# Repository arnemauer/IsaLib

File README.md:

IsaLib
======

ISA Home control

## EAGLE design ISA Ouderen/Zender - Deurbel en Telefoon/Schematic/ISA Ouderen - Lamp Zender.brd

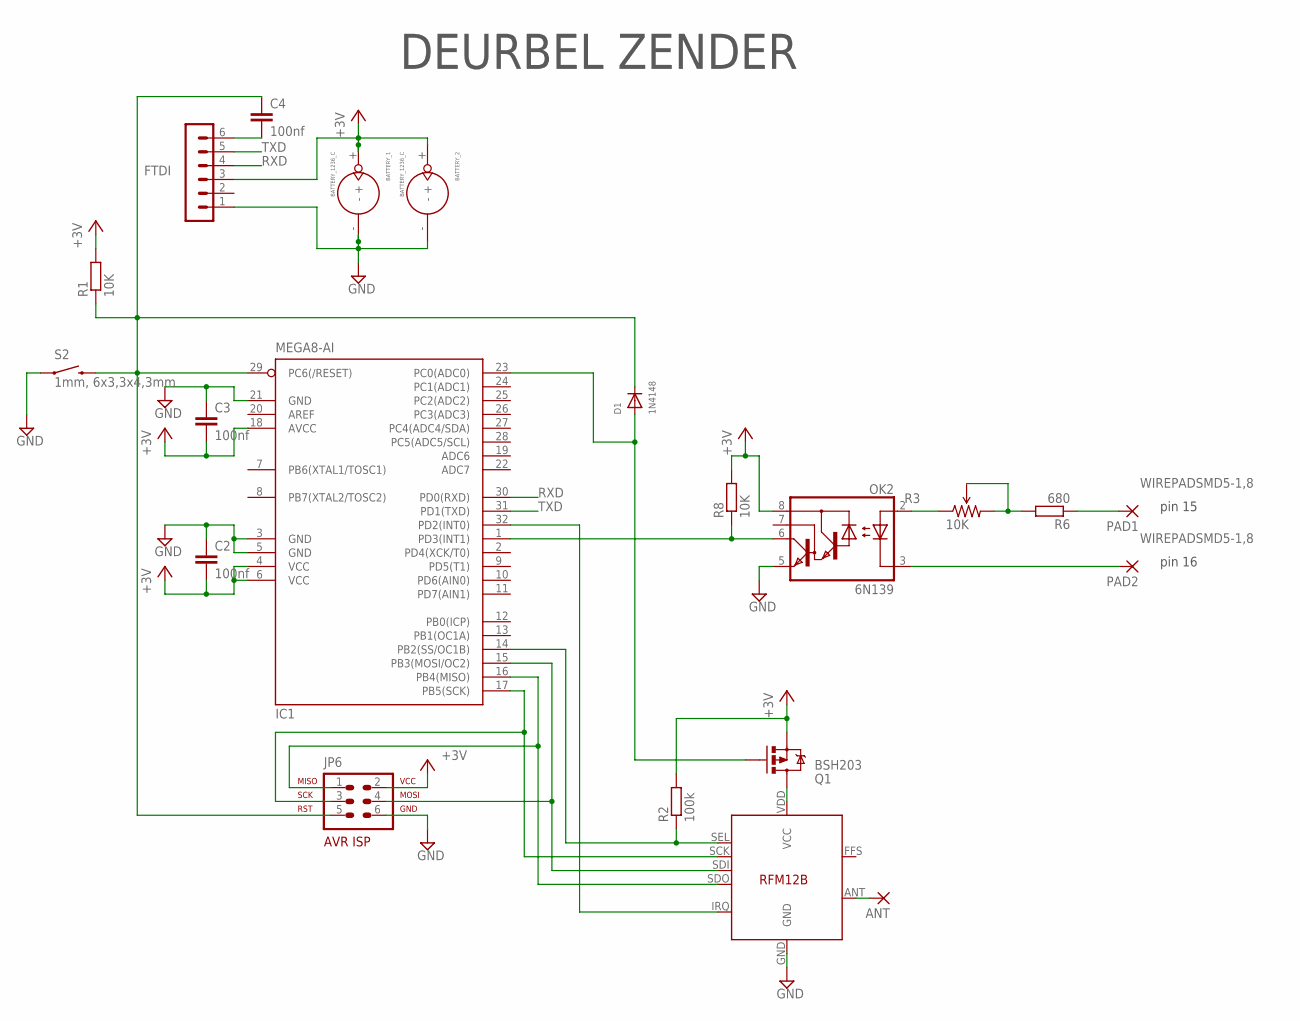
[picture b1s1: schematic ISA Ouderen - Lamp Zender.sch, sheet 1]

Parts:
ANT: 1,6/0,8
BATTERY_1, BATTERY_2: BATTERY_1236_C
C2, C3, C4: 100nf; C0805
D1: 1N4148; SOD-323F
FTDI: FTDI; MA06-1
IC1: MEGA8-AI; TQFP32-08@1
JP6: AVR-ISP-6VERT; AVR-ISP-6
OK2: 6N139; SOIC08
PAD1, PAD2: WIREPADSMD5-1,8; 5-1,8
Q1: BSH203; SOT23
R1, R8: 10K; R0805
R2: 100k; R0805
R3: 10K; TRIMPOT-5MM-V2
R6: 680; R0805
S2: 1mm, 6x3,3x4,3mm; TACTILE-SWITCH-1101NE
U$3: RFM12B

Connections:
+3V3: BATTERY_1.+, BATTERY_2.+, C2.2, C3.2, FTDI.3, IC1.4 (VCC), IC1.6 (VCC), IC1.18 (AVCC), JP6.2, OK2.8 (VCC), Q1.2 (S), R1.2, R2.2, R8.2; also elsewhere on the board
GND: BATTERY_1.-, BATTERY_2.-, C2.1, C3.1, FTDI.1, IC1.3 (GND), IC1.5 (GND), IC1.21 (GND), JP6.6, OK2.5 (GND), S2.P$1 (1), U$3.GND; also elsewhere on the board
unnamed: Q1.3 (D), U$3.VDD (VCC)
unnamed: D1.A, IC1.23 (PC0(ADC0)), Q1.1 (G)
unnamed: ANT.1, U$3.ANT
unnamed: IC1.14 (PB2(SS/OC1B)), R2.1, U$3.SEL
unnamed: IC1.32 (PD2(INT0)), U$3.IRQ
unnamed: PAD1.1, R6.1
unnamed: IC1.16 (PB4(MISO)), JP6.1, U$3.SDO
unnamed: OK2.2 (A), R3.A (CCW)
unnamed: IC1.17 (PB5(SCK)), JP6.3, U$3.SCK
unnamed: C4.2, FTDI.6
unnamed: OK2.3 (C), PAD2.1
unnamed: IC1.1 (PD3(INT1)), OK2.6 (VO), R8.1
unnamed: R3.B (WIPER), R3.C (CW), R6.2
unnamed: IC1.15 (PB3(MOSI/OC2)), JP6.4, U$3.SDI
RST: C4.1, D1.C, IC1.29 (PC6(/RESET)), JP6.5, R1.1, S2.P$2 (2)
RXD: FTDI.4, IC1.30 (PD0(RXD)); also elsewhere on the board
TXD: FTDI.5, IC1.31 (PD1(TXD)); also elsewhere on the board

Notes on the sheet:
pin 15
pin 16
DEURBEL ZENDER

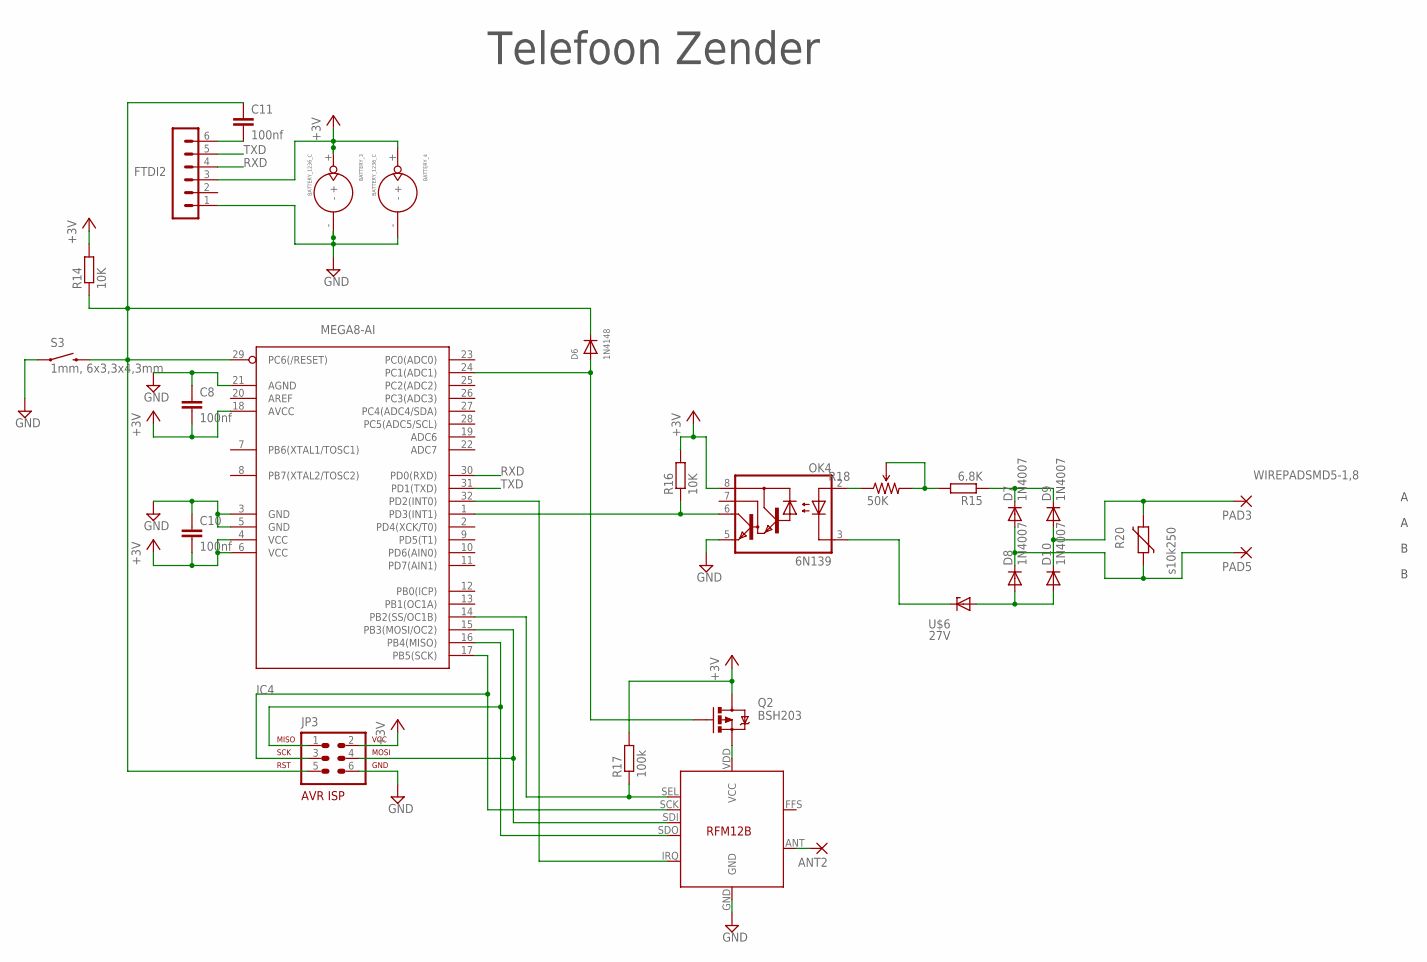
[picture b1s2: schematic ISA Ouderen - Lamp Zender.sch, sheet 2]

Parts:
ANT2: 1,6/0,8
BATTERY_3, BATTERY_4: BATTERY_1236_C
C8, C10, C11: 100nf; C0805
D6: 1N4148; SOD-323F
D7, D8, D9, D10: 1N4007; DO214BA
FTDI2: FTDI; MA06-1
IC4: MEGA8-AI; TQFP32-08
JP3: AVR-ISP-6VERT; AVR-ISP-6
OK4: 6N139; SOIC08
PAD3, PAD5: WIREPADSMD5-1,8; 5-1,8
Q2: BSH203; SOT23
R14, R16: 10K; R0805
R15: 6.8K; R0805
R17: 100k; R0805
R18: 50K; TRIMPOT-5MM-V2
R20: s10k250; R-7,5
S3: 1mm, 6x3,3x4,3mm; TACTILE-SWITCH-1101NE
U$5: RFM12B
U$6: 27V; ZDIO-2.5

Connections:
+3V3: BATTERY_3.+, BATTERY_4.+, C8.2, C10.2, FTDI2.3, IC4.4 (VCC), IC4.6 (VCC), IC4.18 (AVCC), JP3.2, OK4.8 (VCC), Q2.3 (D), R14.2, R16.2, R17.2; also elsewhere on the board
GND: BATTERY_3.-, BATTERY_4.-, C8.1, C10.1, FTDI2.1, IC4.3 (GND), IC4.5 (GND), IC4.21 (AGND), JP3.6, OK4.5 (GND), S3.P$1 (1), U$5.GND; also elsewhere on the board
unnamed: IC4.14 (PB2(SS/OC1B)), R17.1, U$5.SEL
unnamed: IC4.32 (PD2(INT0)), U$5.IRQ
unnamed: C11.2, FTDI2.6
unnamed: IC4.15 (PB3(MOSI/OC2)), JP3.4, U$5.SDI
unnamed: ANT2.1, U$5.ANT
unnamed: IC4.16 (PB4(MISO)), JP3.1, U$5.SDO
unnamed: IC4.17 (PB5(SCK)), JP3.3, U$5.SCK
unnamed: OK4.2 (A), R18.A (CCW)
unnamed: OK4.3 (C), U$6.C
unnamed: IC4.1 (PD3(INT1)), OK4.6 (VO), R16.1
unnamed: R15.2, R18.B (WIPER), R18.C (CW)
unnamed: Q2.2 (S), U$5.VDD (VCC)
unnamed: D6.A, IC4.24 (PC1(ADC1)), Q2.1 (G)
unnamed: D9.A, D10.C, PAD3.1, R20.2
unnamed: D7.A, D8.C, PAD5.1, R20.1
unnamed: D8.A, D10.A, U$6.A
unnamed: D7.C, D9.C, R15.1
RST2: C11.1, D6.C, IC4.29 (PC6(/RESET)), JP3.5, R14.1, S3.P$2 (2)
RXD: FTDI2.4, IC4.30 (PD0(RXD)); also elsewhere on the board
TXD: FTDI2.5, IC4.31 (PD1(TXD)); also elsewhere on the board

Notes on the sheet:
Telefoon Zender

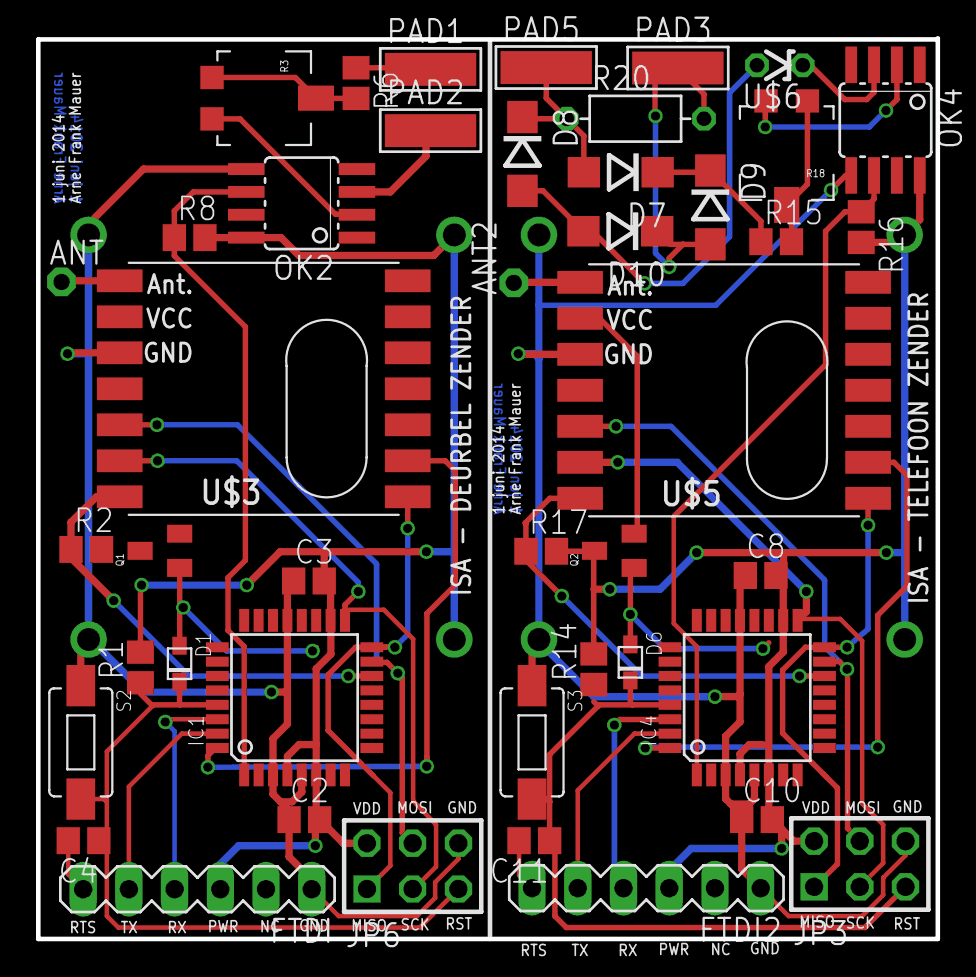
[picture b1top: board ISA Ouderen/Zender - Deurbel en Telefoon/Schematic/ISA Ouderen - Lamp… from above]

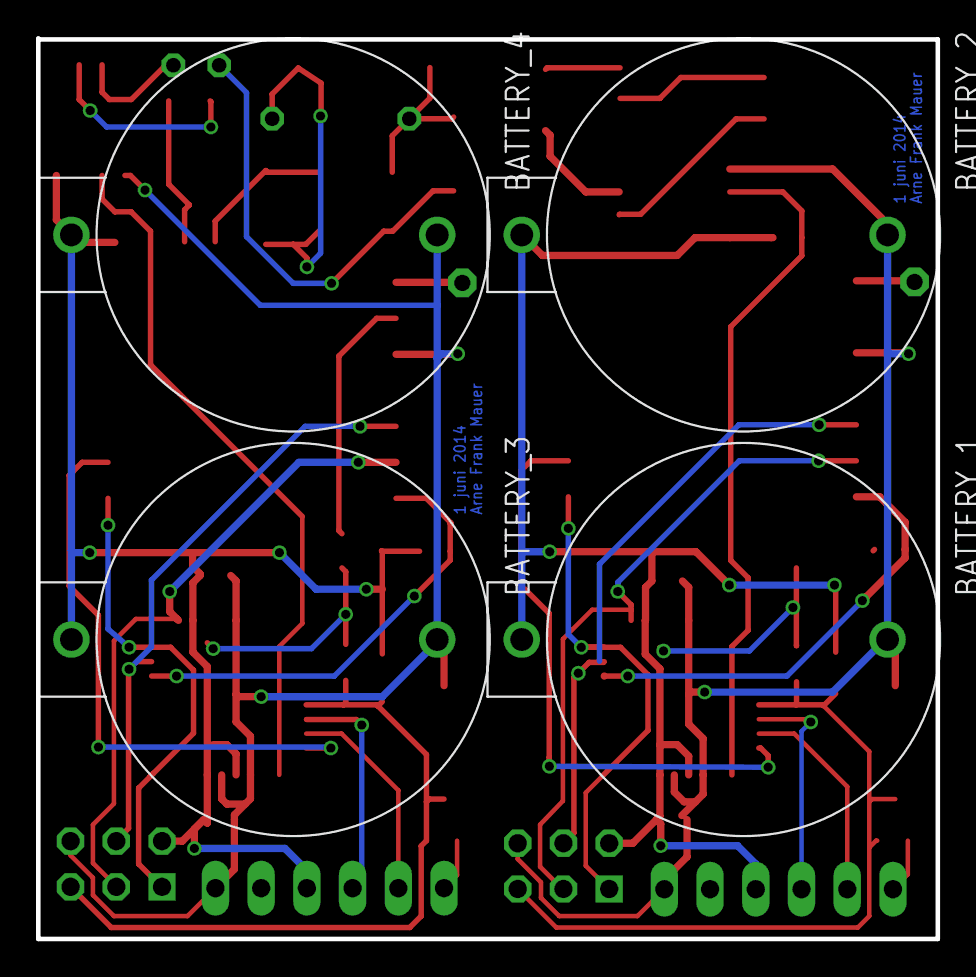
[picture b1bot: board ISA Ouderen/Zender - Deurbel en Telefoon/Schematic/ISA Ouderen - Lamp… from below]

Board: 2 copper layers, 50.0 x 50.0 mm, 48 parts (4 on the bottom side), 37 nets.

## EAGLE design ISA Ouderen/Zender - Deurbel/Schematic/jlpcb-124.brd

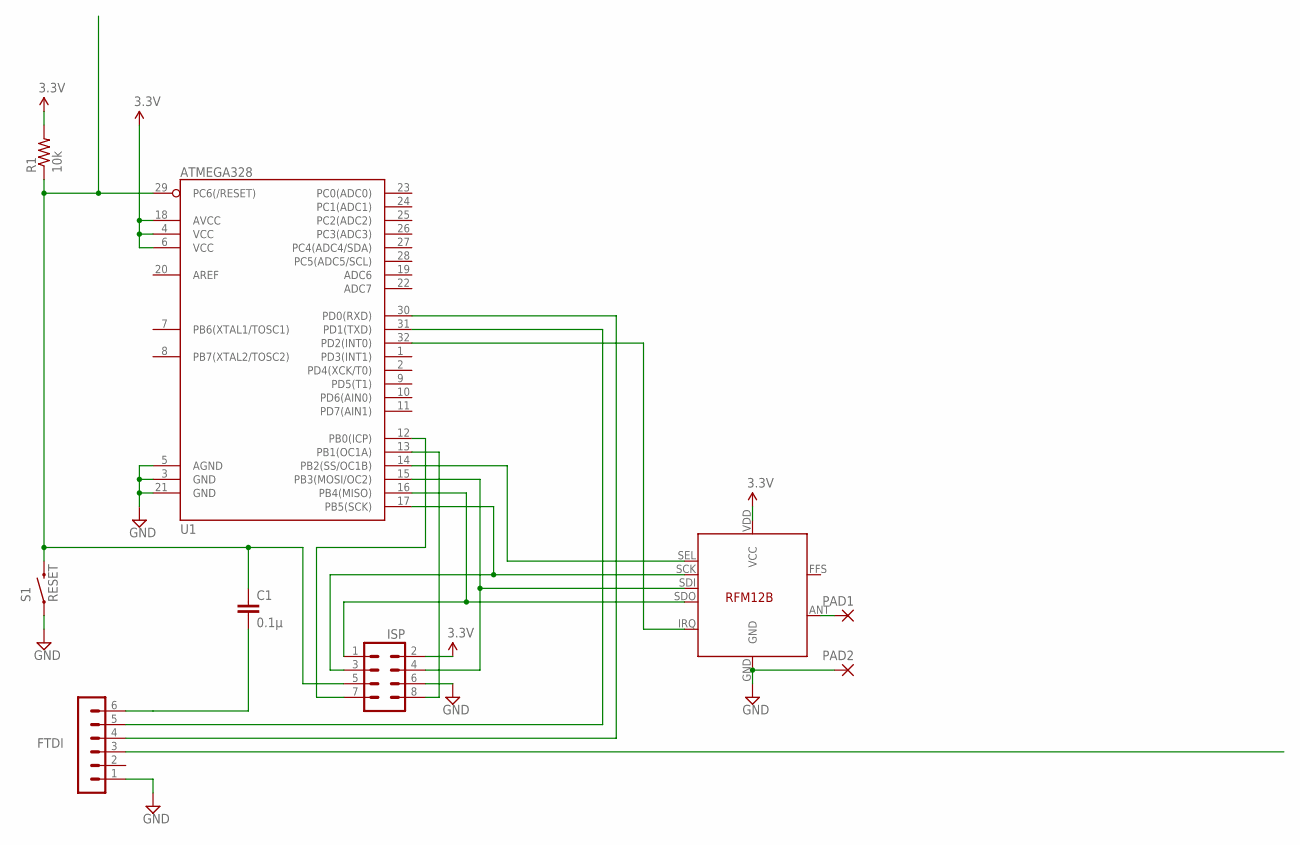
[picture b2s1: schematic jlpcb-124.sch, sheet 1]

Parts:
C1: 0.1µ; 0603-CAP
FTDI: FTDI; MA06-1
PAD1, PAD2: 1,6/0,8
R1: 10k; 0603-RES
S1: RESET; TACTILE-SWITCH-1101NE
SV7: ISP; MA04-2
U1: ATMEGA328; TQFP32-08
U$1: RFM12B

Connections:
3.3V: R1.2, SV7.2, U1.4 (VCC), U1.6 (VCC), U1.18 (AVCC), U$1.VDD (VCC)
GND: FTDI.1, PAD2.1, S1.P$1 (1), SV7.6, U1.3 (GND), U1.5 (AGND), U1.21 (GND), U$1.GND; also elsewhere on the board
unnamed: SV7.1, U1.16 (PB4(MISO)), U$1.SDO
unnamed: SV7.4, U1.15 (PB3(MOSI/OC2)), U$1.SDI
unnamed: U1.14 (PB2(SS/OC1B)), U$1.SEL
unnamed: SV7.3, U1.17 (PB5(SCK)), U$1.SCK
unnamed: SV7.8, U1.13 (PB1(OC1A))
unnamed: U1.32 (PD2(INT0)), U$1.IRQ
unnamed: PAD1.1, U$1.ANT
unnamed: C1.2, FTDI.6
unnamed: SV7.7, U1.12 (PB0(ICP))
PWR: FTDI.3
RST: C1.1, R1.1, S1.P$2 (2), SV7.5, U1.29 (PC6(/RESET))
RXD: FTDI.4, U1.30 (PD0(RXD)); also elsewhere on the board
TXD: FTDI.5, U1.31 (PD1(TXD)); also elsewhere on the board

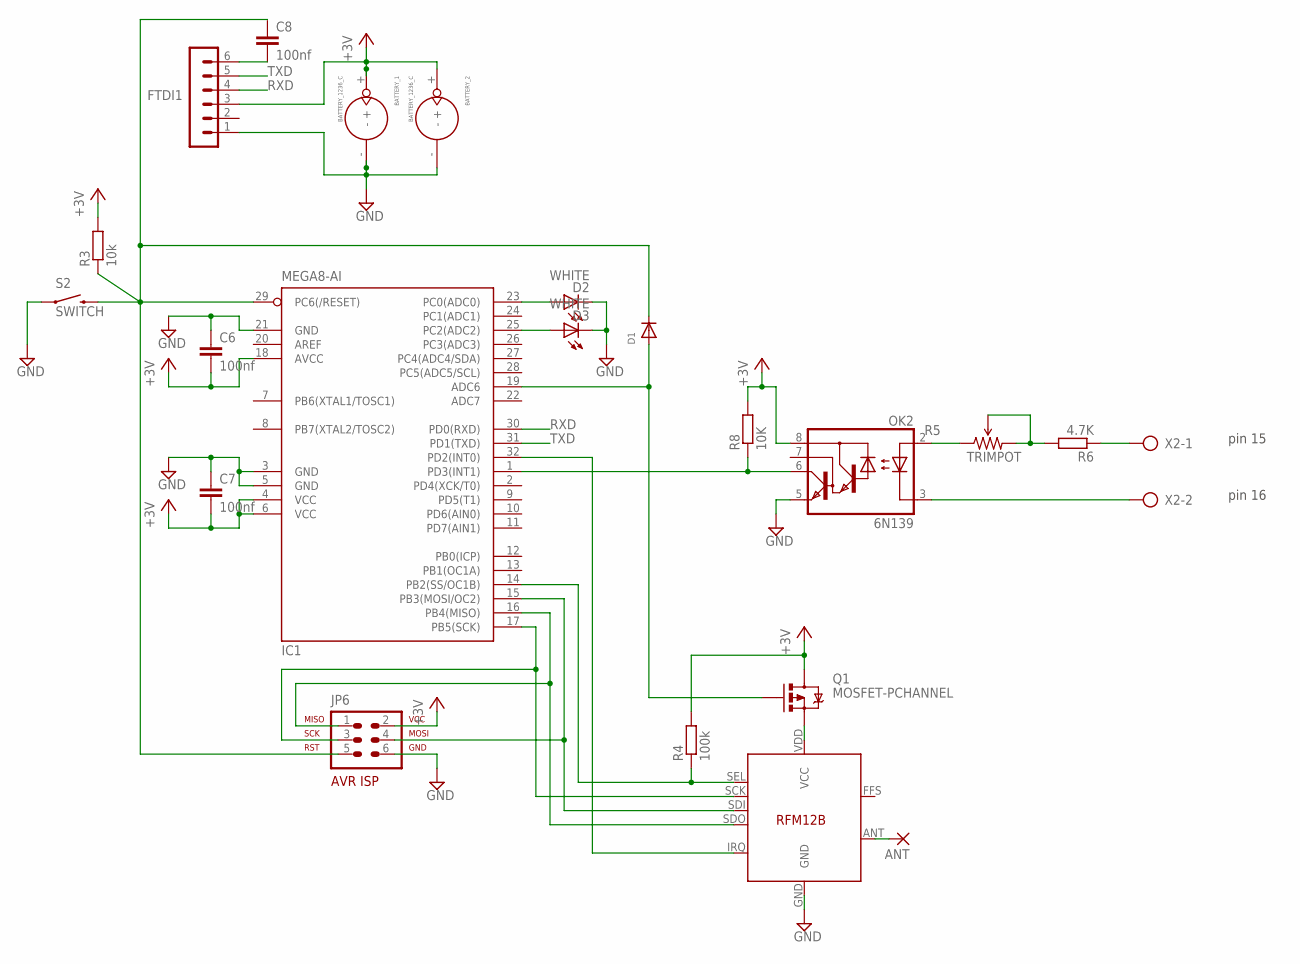
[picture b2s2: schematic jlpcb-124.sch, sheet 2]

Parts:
ANT: 1,6/0,8
BATTERY_1, BATTERY_2: BATTERY_1236_C
C6, C7, C8: 100nf; C0805
D1: DIODESOD-323F; SOD-323F
D2, D3: WHITE; LED-1206
FTDI1: FTDI; MA06-1
IC1: MEGA8-AI; TQFP32-08
JP6: AVR-ISP-6VERT; AVR-ISP-6
OK2: 6N139; DIL08
Q1: MOSFET-PCHANNEL; SOT23
R3: 10k; R0805
R4: 100k; R0805
R5: TRIMPOT; TRIMPOT-5MM-V2
R6: 4.7K; R0805
R8: 10K; R0805
S2: SWITCH; TACTILE-SWITCH-1101NE
U$3: RFM12B
X2: AK300/2

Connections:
+3V3: BATTERY_1.+, BATTERY_2.+, C6.2, C7.2, FTDI1.3, IC1.4 (VCC), IC1.6 (VCC), IC1.18 (AVCC), JP6.2, OK2.8 (VCC), Q1.3 (D), R3.2, R4.2, R8.2
GND: BATTERY_1.-, BATTERY_2.-, C6.1, C7.1, D2.C, D3.C, FTDI1.1, IC1.3 (GND), IC1.5 (GND), IC1.21 (GND), JP6.6, OK2.5 (GND), S2.P$1 (1), U$3.GND; also elsewhere on the board
unnamed: IC1.14 (PB2(SS/OC1B)), R4.1, U$3.SEL
unnamed: IC1.32 (PD2(INT0)), U$3.IRQ
unnamed: C8.2, FTDI1.6
unnamed: ANT.1, U$3.ANT
unnamed: IC1.16 (PB4(MISO)), JP6.1, U$3.SDO
unnamed: IC1.17 (PB5(SCK)), JP6.3, U$3.SCK
unnamed: R6.1, X2.1
unnamed: OK2.2 (A), R5.A (CCW)
unnamed: OK2.3 (C), X2.2
unnamed: IC1.1 (PD3(INT1)), OK2.6 (VO), R8.1
unnamed: R5.B (WIPER), R5.C (CW), R6.2
unnamed: Q1.2 (S), U$3.VDD (VCC)
unnamed: D1.A, IC1.19 (ADC6), Q1.1 (G)
unnamed: D2.A, IC1.23 (PC0(ADC0))
unnamed: D3.A, IC1.25 (PC2(ADC2))
unnamed: IC1.15 (PB3(MOSI/OC2)), JP6.4, U$3.SDI
RST1: C8.1, D1.C, IC1.29 (PC6(/RESET)), JP6.5, R3.1, S2.P$2 (2)
RXD: FTDI1.4, IC1.30 (PD0(RXD)); also elsewhere on the board
TXD: FTDI1.5, IC1.31 (PD1(TXD)); also elsewhere on the board

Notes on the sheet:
pin 15
pin 16

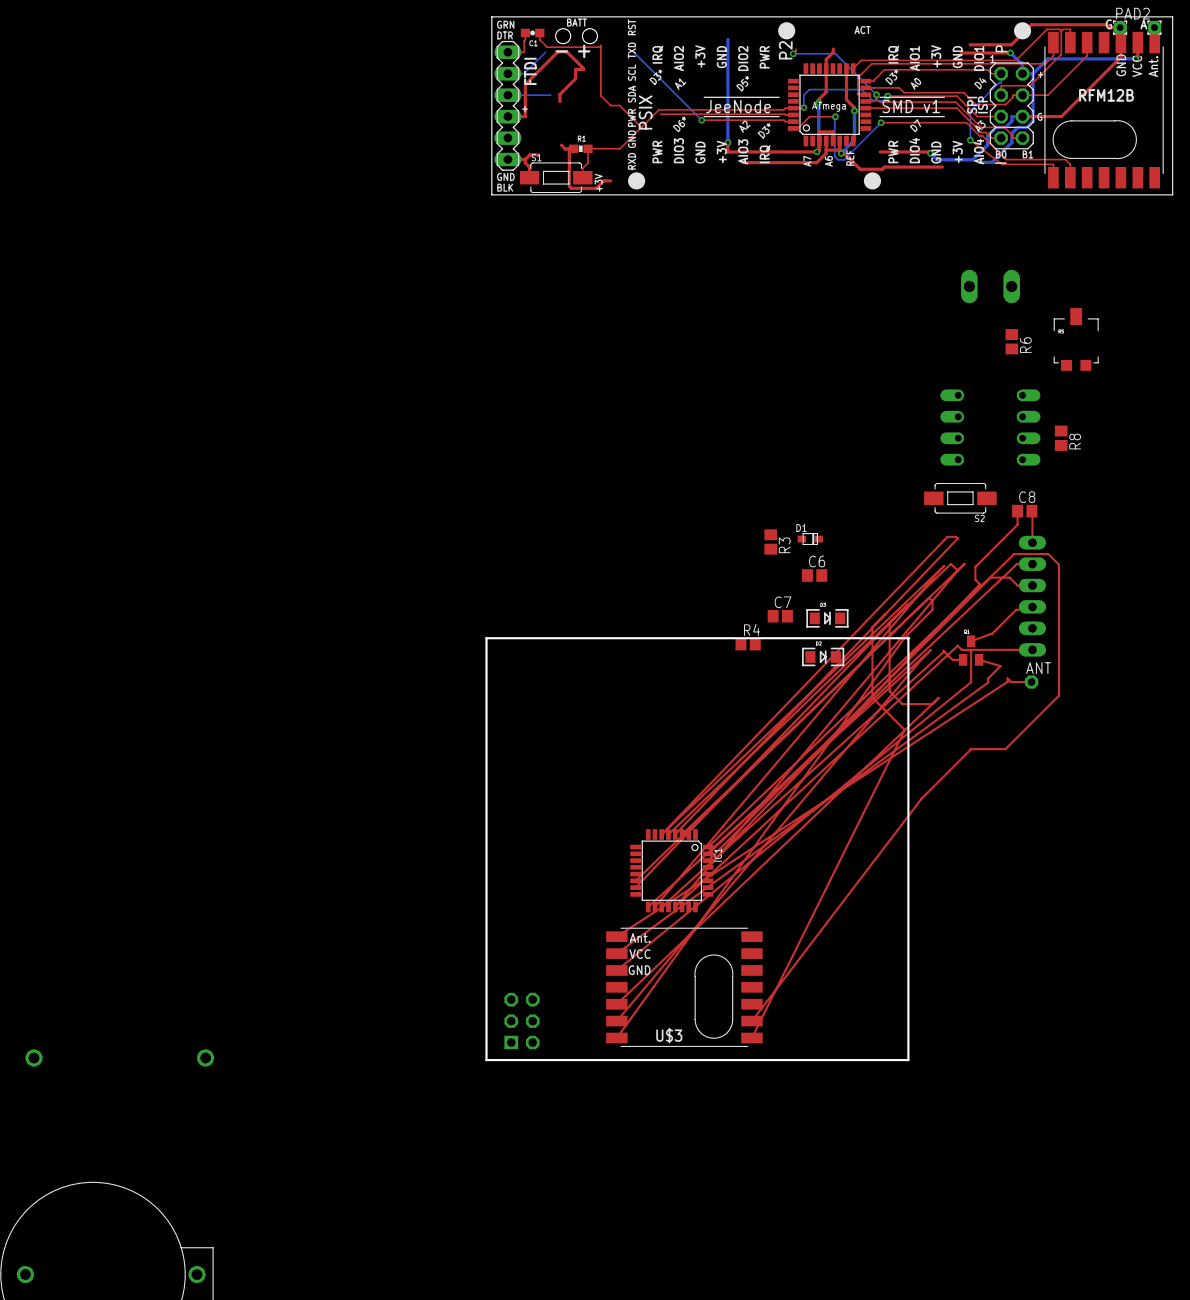
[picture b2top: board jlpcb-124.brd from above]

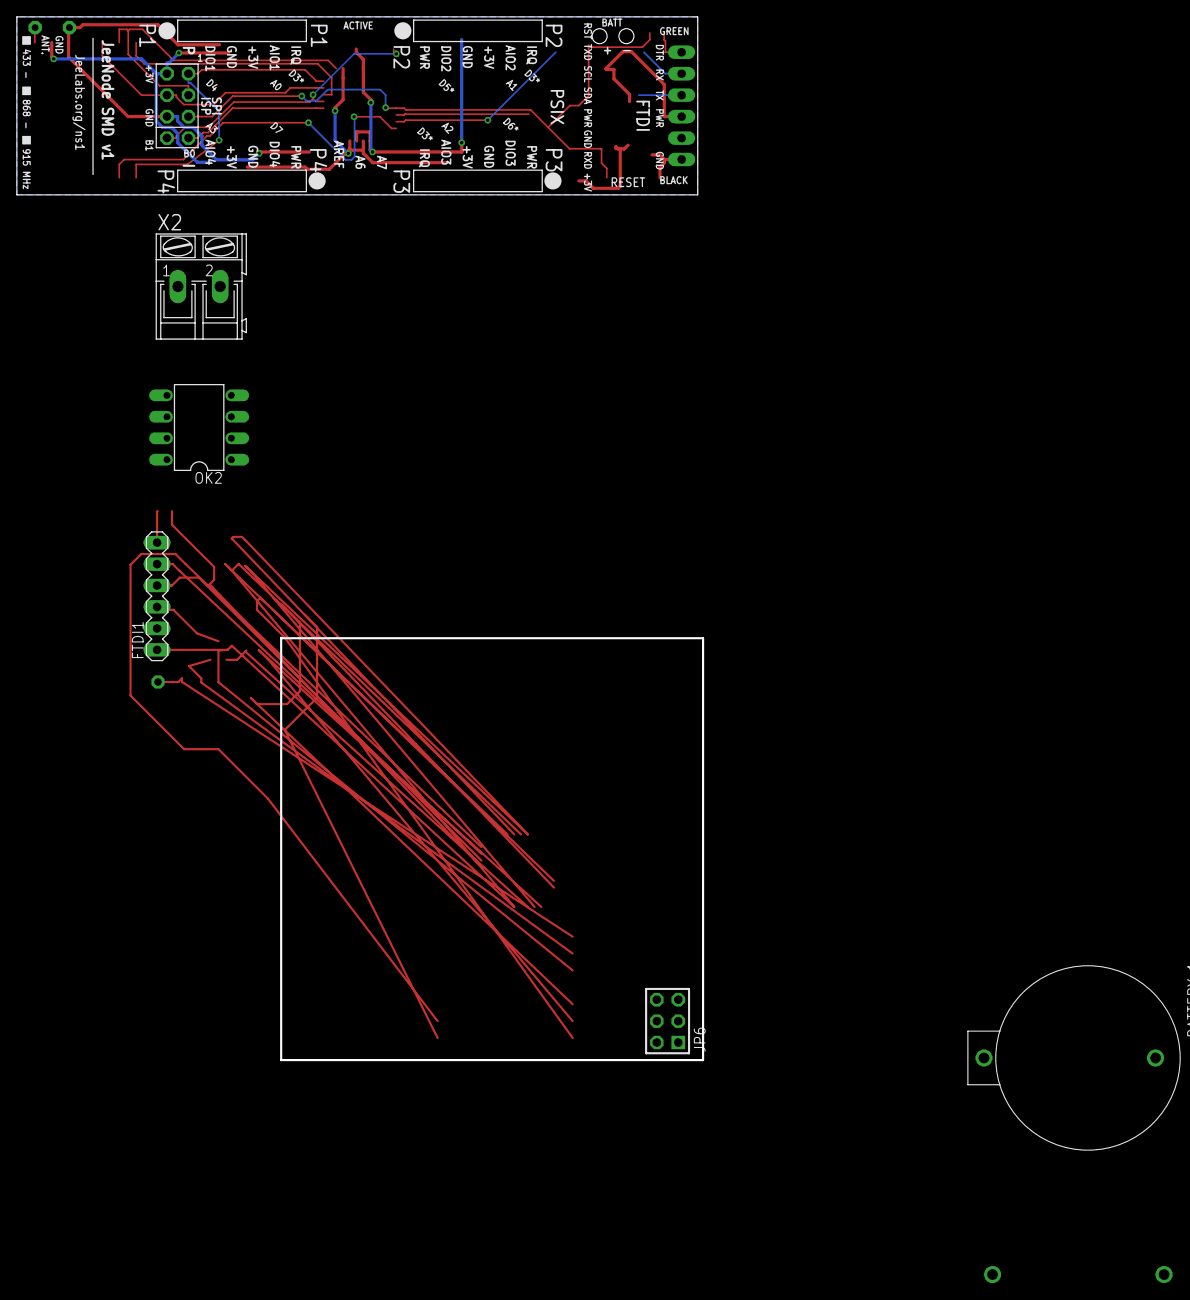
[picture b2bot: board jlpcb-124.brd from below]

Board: 2 copper layers, 81.3 x 123.6 mm, 31 parts (5 on the bottom side), 32 nets.

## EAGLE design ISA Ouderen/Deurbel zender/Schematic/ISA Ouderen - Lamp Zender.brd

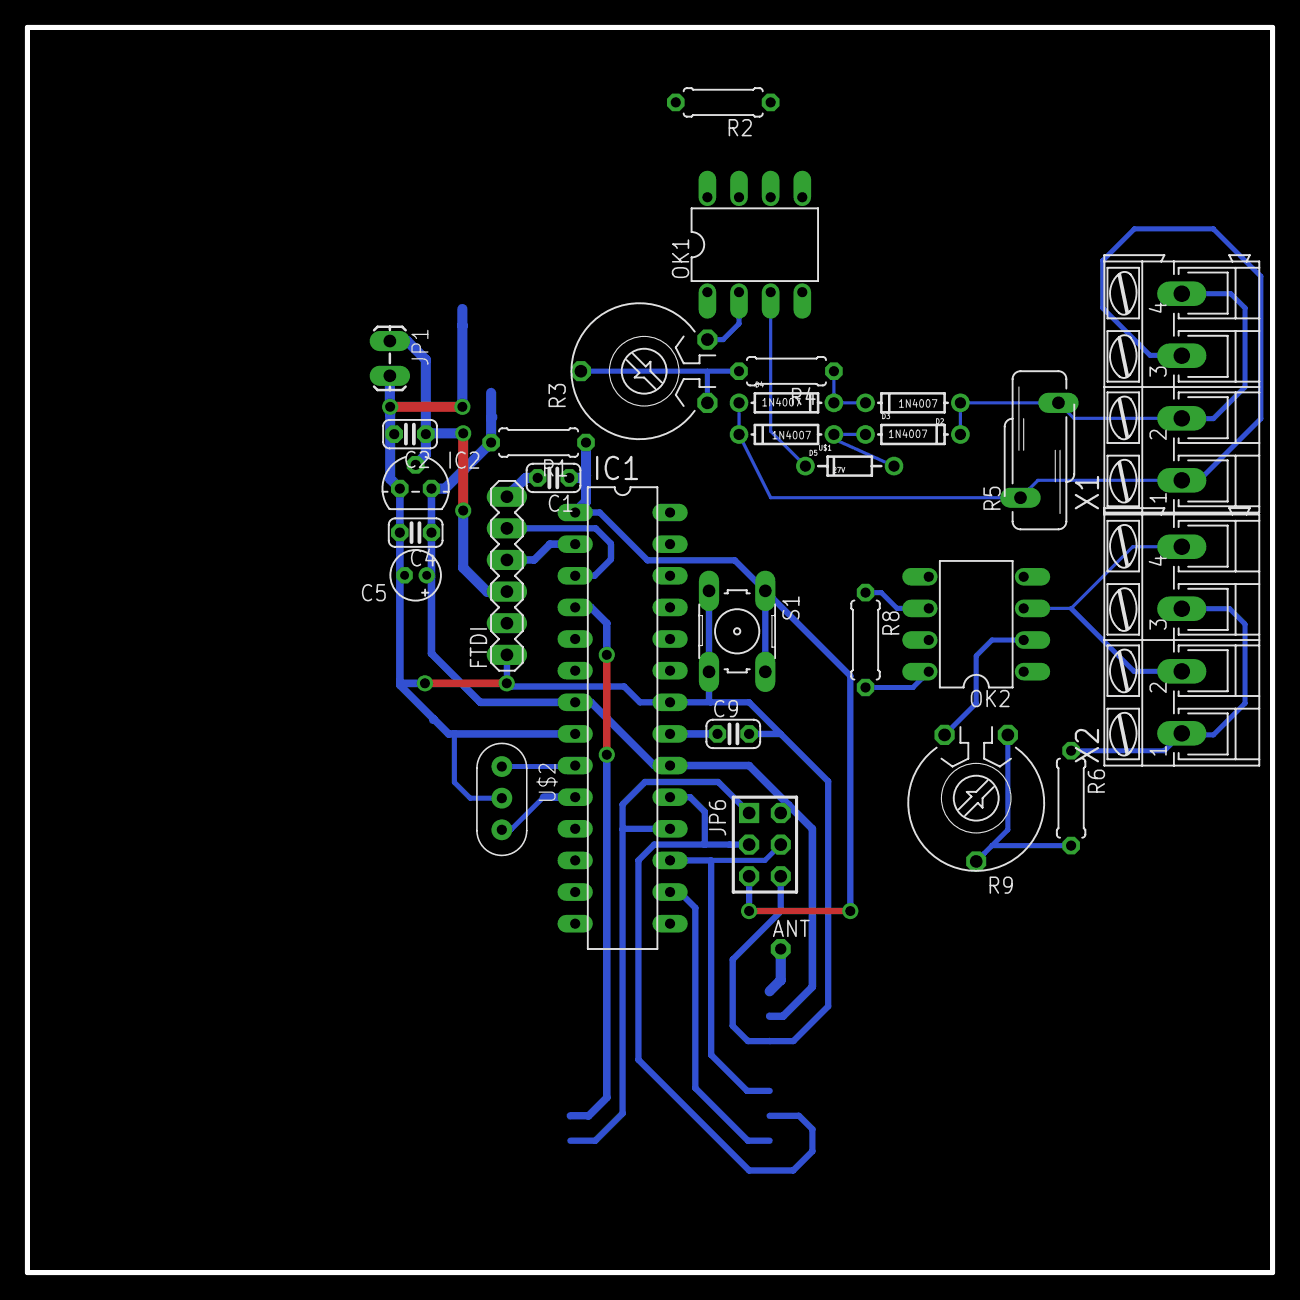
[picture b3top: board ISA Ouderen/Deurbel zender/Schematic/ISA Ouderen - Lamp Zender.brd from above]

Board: 2 copper layers, 100.0 x 100.0 mm, 31 parts (1 on the bottom side), 29 nets.

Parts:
ANT: 1,6/0,8
C1: 100nF; C025-024X044
C2, C4, C9: 100nf; C025-024X044
C5: 10µ; E1,8-4
D2, D3, D4, D5: 1N4007; DO-1N4148
FTDI: FTDI; MA06-1
IC1: MEGA8-P; DIL28-3
IC2: MCP1702-33; TO92
JP1: BATT; 1X02_LOCK_LONGPADS
JP6: AVR-ISP-6VERT; AVR-ISP-6
OK1, OK2: 6N138; DIL08
R1: 10k; 0207/7
R2, R8: 10K; 0207/7
R3, R9: PT-10
R4, R6: 4.7K; 0207/7
R5: S10K250
S1: B3F-10XX
U$1: 27V; DIODE-ZENER
U$2: 16mhz; CERM_OSC
U$3: RFM12B
X1, X2: AK300/4

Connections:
+3V3: C4.1, C5.+, IC1.7, IC1.20, IC2.3, JP6.2, OK1.8, OK2.8, R1.2, R2.2, R8.2, U$3.VDD
GND: C2.2, C4.2, C5.-, C9.2, FTDI.1, IC1.8, IC1.22, IC2.1, JP1.2, JP6.6, OK1.5, OK2.5, S1.3, S1.4, U$2.P$2, U$3.GND
unnamed: IC1.9, U$2.P$1
unnamed: D4.A, D5.C, R5.1, X1.1, X1.3
unnamed: ANT.1, U$3.ANT
unnamed: IC1.16, U$3.SEL
unnamed: D2.A, D3.C, R5.2, X1.2, X1.4
unnamed: OK1.2, R3.E
unnamed: IC1.4, U$3.IRQ
unnamed: OK1.3, U$1.P$1
unnamed: OK1.6, R2.1
unnamed: R3.A, R3.S, R4.2
unnamed: R6.1, X2.1, X2.3
unnamed: IC1.18, JP6.1, U$3.SDO
unnamed: D3.A, D5.A, U$1.P$2
unnamed: D2.C, D4.C, R4.1
unnamed: OK2.2, R9.E
unnamed: IC1.19, JP6.3, U$3.SCK
unnamed: C1.2, FTDI.6
unnamed: IC1.10, U$2.P$3
unnamed: OK2.3, X2.2, X2.4
unnamed: OK2.6, R8.1
unnamed: R6.2, R9.A, R9.S
unnamed: C9.1, IC1.21
unnamed: IC1.17, JP6.4, U$3.SDI
RST: C1.1, IC1.1, JP6.5, R1.1, S1.1, S1.2
RXD: FTDI.4, IC1.2
TXD: FTDI.5, IC1.3
VCC: C2.1, FTDI.3, IC2.2, JP1.1

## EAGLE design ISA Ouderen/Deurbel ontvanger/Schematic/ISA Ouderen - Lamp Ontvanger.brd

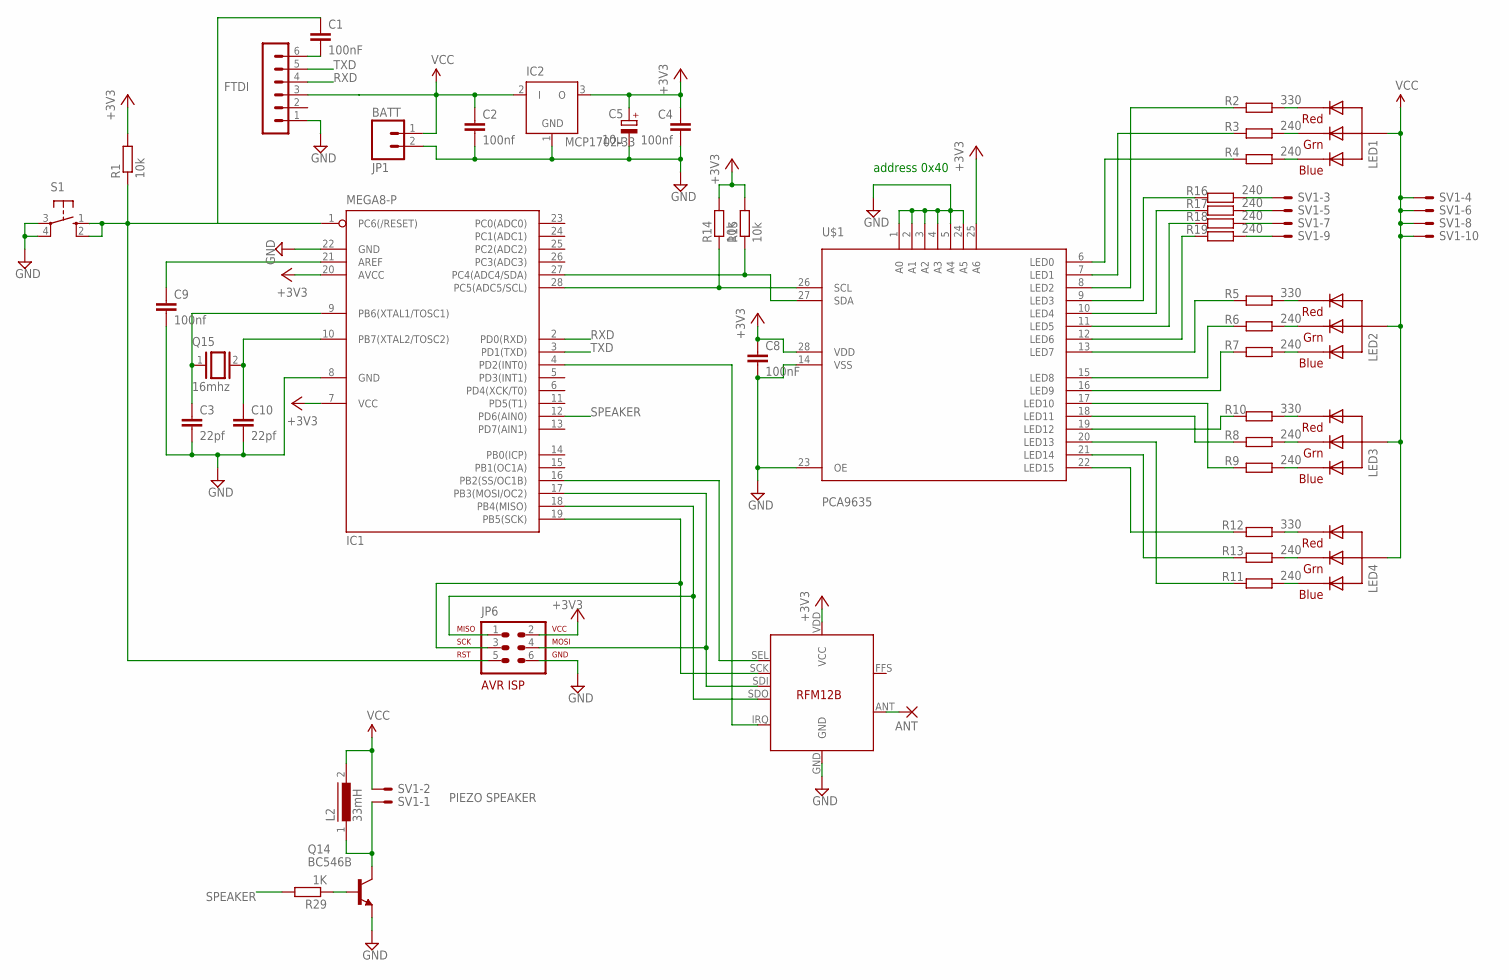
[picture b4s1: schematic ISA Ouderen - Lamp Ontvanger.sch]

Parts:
ANT: 1,6/0,8
C1, C8: 100nF; C025-024X044
C2, C4, C9: 100nf; C025-024X044
C3, C10: 22pf; C025-024X044
C5: 10µ; E1,8-4
FTDI: FTDI; MA06-1
IC1: MEGA8-P; DIL28-3
IC2: MCP1702-33; TO92
JP1: BATT; 1X02_LOCK_LONGPADS
JP6: AVR-ISP-6VERT; AVR-ISP-6
L2: 33mH; 82114R
LED1, LED2, LED3, LED4: RGBLED_CA-5MM; LED5MMRGB
Q14: BC546B; TO92-EBC
Q15: 16mhz; QS
R1, R14, R15: 10k; 0207/7
R2, R5, R10, R12: 330; 0207/7
R3, R4, R6, R7, R8, R9, R11, R13: 240; 0207/7
R16, R17, R18, R19: 240; 0207/2V
R29: 1K; 0207/7
S1: 10-XX; B3F-10XX
SV1: ML10LE; ML10L
U$1: PCA9635
U$3: RFM12B

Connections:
+3V3: C4.1, C5.+, C8.1, IC1.7 (VCC), IC1.20 (AVCC), IC2.3 (O), JP6.2, R1.2, R14.2, R15.2, U$1.25 (A6), U$1.28 (VDD), U$3.VDD (VCC)
GND: C2.2, C3.2, C4.2, C5.-, C8.2, C9.2, C10.2, FTDI.1, IC1.8 (GND), IC1.22 (GND), IC2.1 (GND), JP1.2, JP6.6, Q14.E, S1.3, S1.4 (P1), U$1.1 (A0), U$1.2 (A1), U$1.3 (A2), U$1.4 (A3), U$1.5 (A4), U$1.14 (VSS), U$1.23 (OE), U$1.24 (A5), U$3.GND
unnamed: C3.1, IC1.9 (PB6(XTAL1/TOSC1)), Q15.1
unnamed: IC1.28 (PC5(ADC5/SCL)), R14.1, U$1.26 (SCL)
unnamed: ANT.1, U$3.ANT
unnamed: IC1.16 (PB2(SS/OC1B)), U$3.SEL
unnamed: LED1.1 (RED), R2.2
unnamed: LED1.3 (GREEN), R3.2
unnamed: IC1.4 (PD2(INT0)), U$3.IRQ
unnamed: LED1.4 (BLUE), R4.2
unnamed: LED2.1 (RED), R5.2
unnamed: IC1.27 (PC4(ADC4/SDA)), R15.1, U$1.27 (SDA)
unnamed: LED2.3 (GREEN), R6.2
unnamed: LED2.4 (BLUE), R7.2
unnamed: IC1.18 (PB4(MISO)), JP6.1, U$3.SDO
unnamed: LED3.1 (RED), R10.2
unnamed: LED3.3 (GREEN), R8.2
unnamed: LED3.4 (BLUE), R9.2
unnamed: LED4.1 (RED), R12.2
unnamed: LED4.3 (GREEN), R13.2
unnamed: IC1.19 (PB5(SCK)), JP6.3, U$3.SCK
unnamed: C1.2, FTDI.6
unnamed: C10.1, IC1.10 (PB7(XTAL2/TOSC2)), Q15.2
unnamed: LED4.4 (BLUE), R11.2
unnamed: R12.1, U$1.22 (LED15)
unnamed: R13.1, U$1.21 (LED14)
unnamed: R11.1, U$1.20 (LED13)
unnamed: R10.1, U$1.19 (LED12)
unnamed: R16.1, U$1.9 (LED3)
unnamed: R8.1, U$1.18 (LED11)
unnamed: R16.2, SV1.3
unnamed: R7.1, U$1.16 (LED9)
unnamed: R17.1, U$1.10 (LED4)
unnamed: R2.1, U$1.8 (LED2)
unnamed: R3.1, U$1.7 (LED1)
unnamed: R4.1, U$1.6 (LED0)
unnamed: R18.1, U$1.11 (LED5)
unnamed: R19.1, U$1.12 (LED6)
unnamed: R9.1, U$1.17 (LED10)
unnamed: R5.1, U$1.13 (LED7)
unnamed: R17.2, SV1.5
unnamed: R18.2, SV1.7
unnamed: R19.2, SV1.9
unnamed: R6.1, U$1.15 (LED8)
unnamed: C9.1, IC1.21 (AREF)
unnamed: IC1.17 (PB3(MOSI/OC2)), JP6.4, U$3.SDI
unnamed: L2.1, Q14.C, SV1.1
unnamed: Q14.B, R29.1
RST: C1.1, IC1.1 (PC6(/RESET)), JP6.5, R1.1, S1.1 (S), S1.2 (S1)
RXD: FTDI.4, IC1.2 (PD0(RXD))
SPEAKER: IC1.12 (PD6(AIN0)), IC1.14 (PB0(ICP)), R29.2
TXD: FTDI.5, IC1.3 (PD1(TXD))
VCC: C2.1, FTDI.3, IC2.2 (I), JP1.1, L2.2, LED1.2 (VCC), LED2.2 (VCC), LED3.2 (VCC), LED4.2 (VCC), SV1.2, SV1.4, SV1.6, SV1.8, SV1.10

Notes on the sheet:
address 0x40
PIEZO SPEAKER

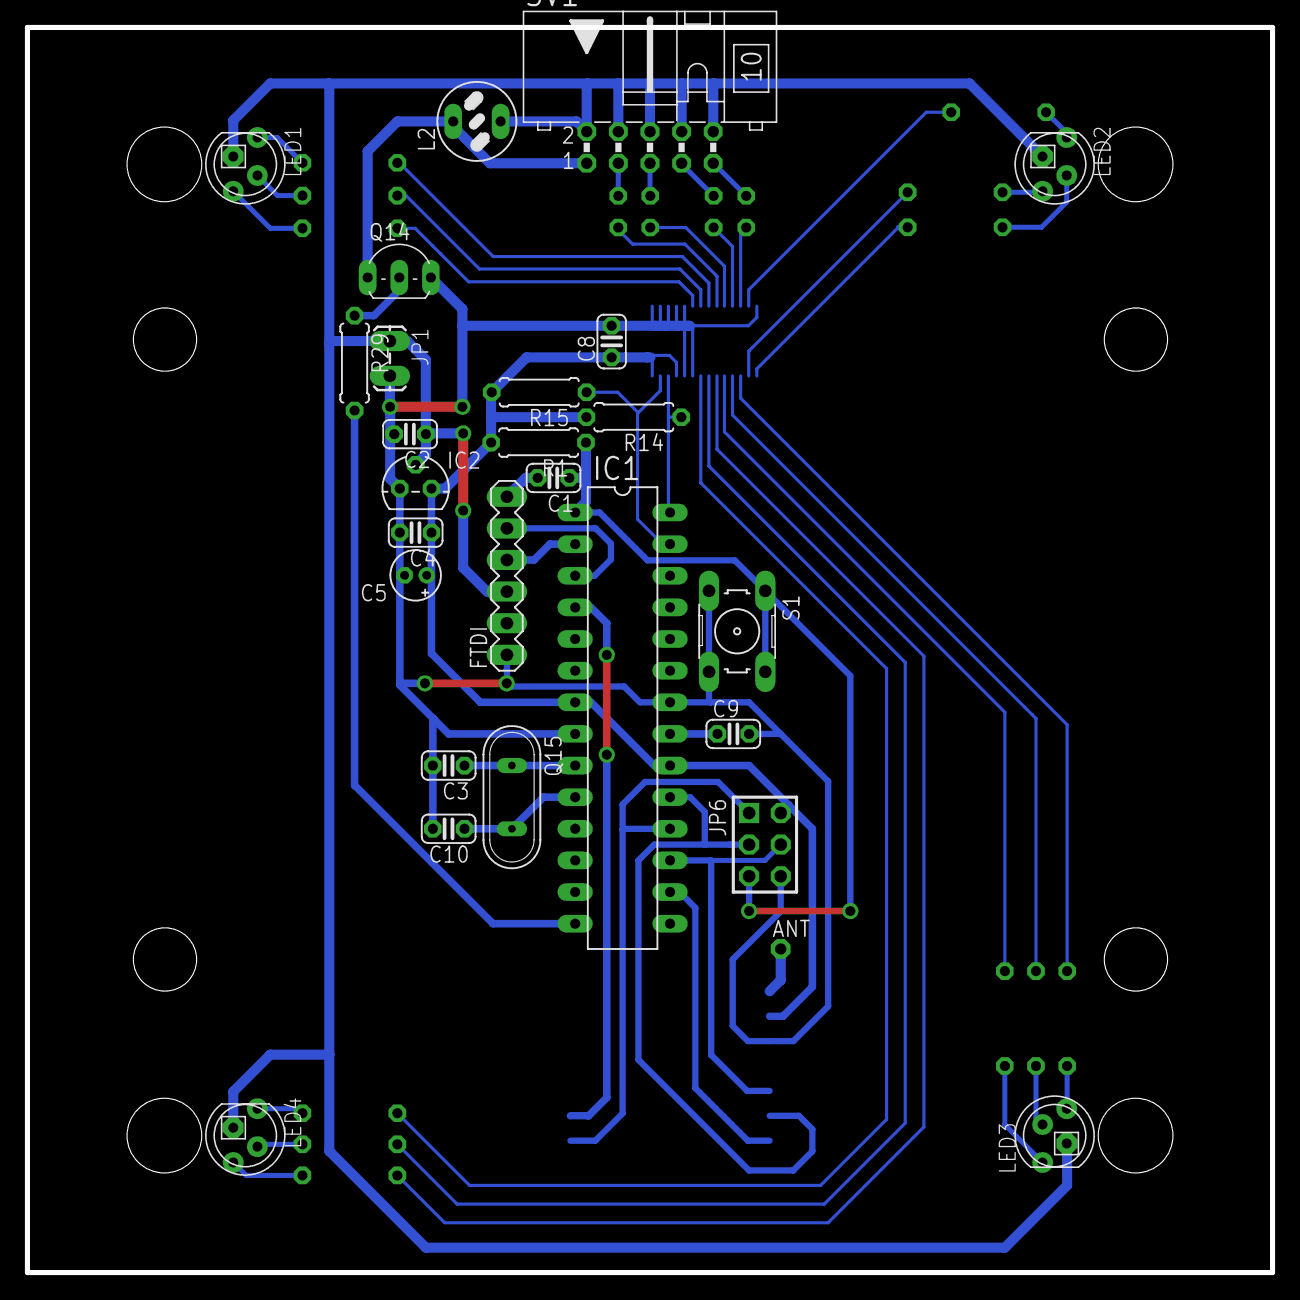
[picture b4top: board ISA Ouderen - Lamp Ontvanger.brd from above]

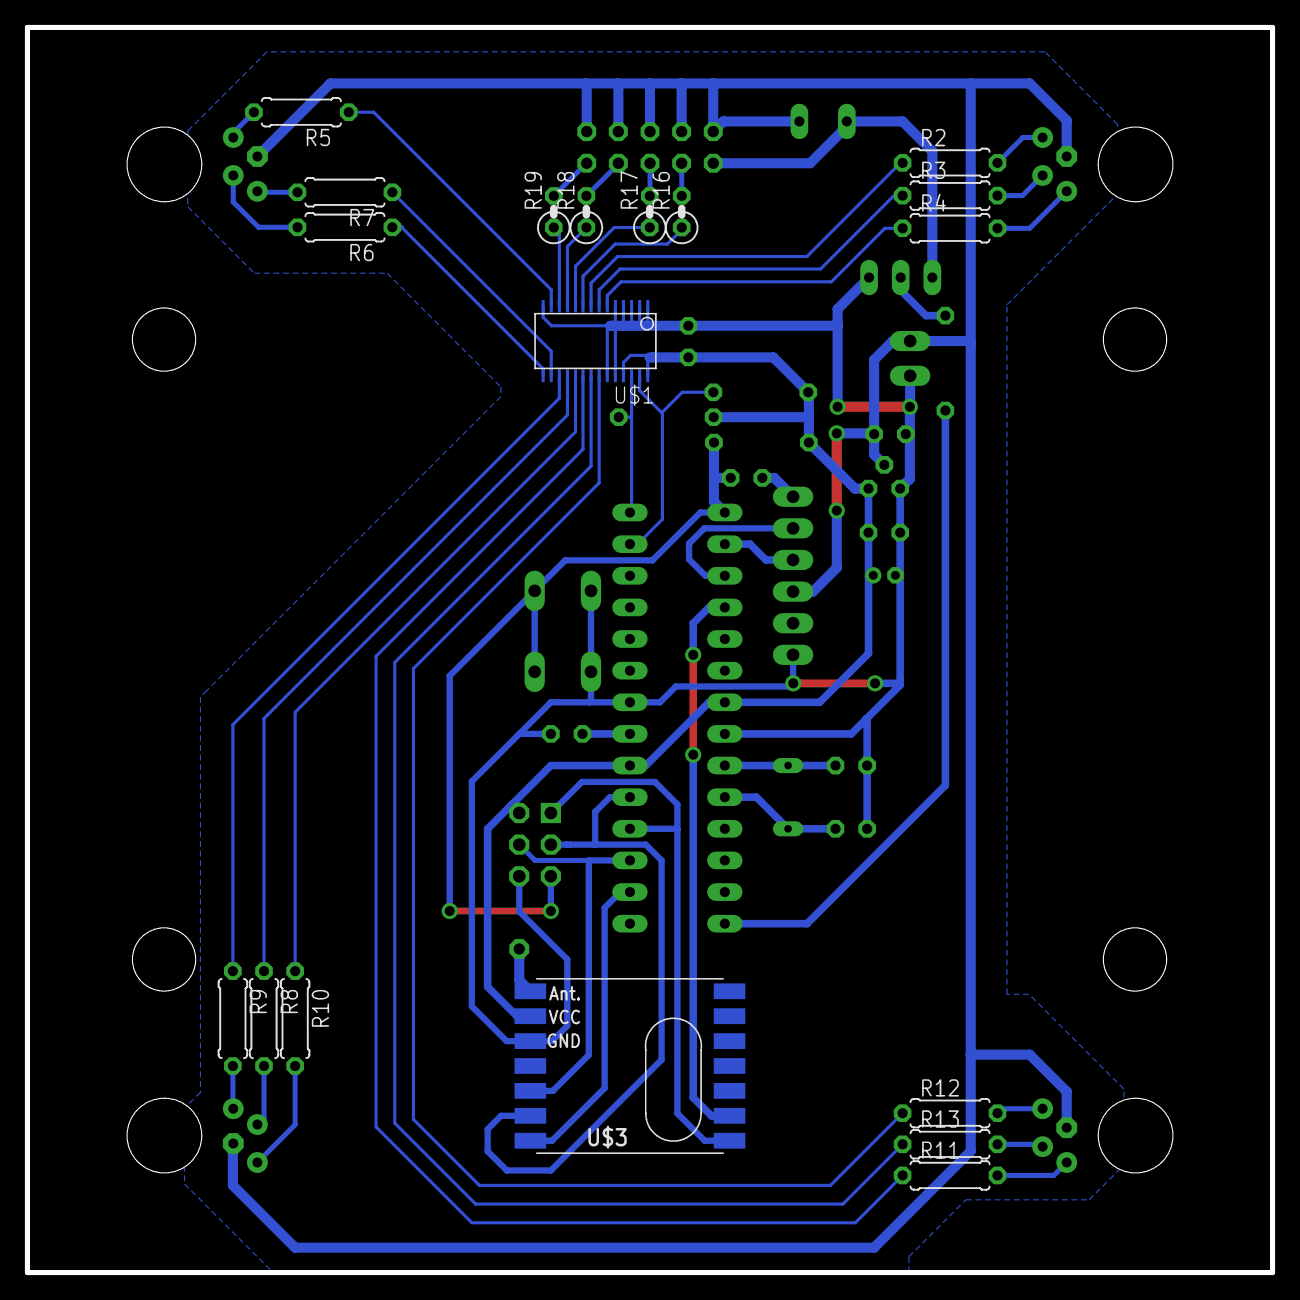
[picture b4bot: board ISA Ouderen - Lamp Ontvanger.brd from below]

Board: 2 copper layers, 100.0 x 100.0 mm, 45 parts (18 on the bottom side), 53 nets.

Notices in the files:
parts and their libraries:
SparkFun-DigitalIC: Licensing: CC v3.0 Share-Alike You are welcome to use this library for commercial purposes.
